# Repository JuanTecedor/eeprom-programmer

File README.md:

This is a fork of the Ben Eater's version of the EEPROM programmer, originally licensed under MIT LICENSE.

I did not like the fact of having it on a breadboard or buying it so I made a PCB.

~~I still have to solder and check that the circuit is working.~~
~~When I'm sure it's working I will upload the KiCad files.~~
It looks like it is working.

TODO:
  I will also do my own version of the code.
  Documentation

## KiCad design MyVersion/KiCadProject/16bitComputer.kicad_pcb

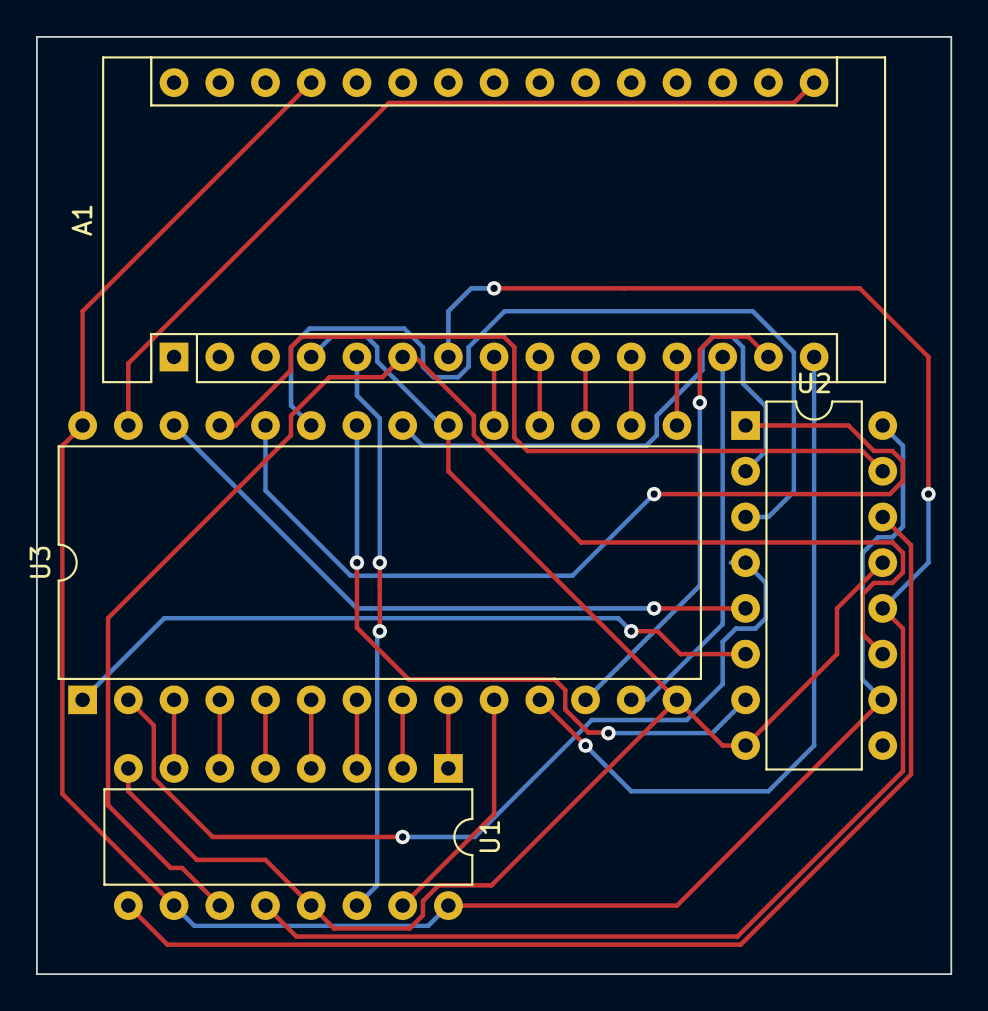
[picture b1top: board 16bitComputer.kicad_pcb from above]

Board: 2 copper layers, 50.8 x 52.1 mm, 4 parts (0 on the bottom side), 31 nets.

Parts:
A1: Arduino_Nano_v3.x; Arduino_Nano
U1, U2: 74HC595; DIP-16_W7.62mm
U3: 28C256; DIP-28_W15.24mm

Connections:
GND: A1.4, U1.8, U1.13, U2.8, U2.13, U3.14, U3.20
unnamed: A1.5, U1.14
unnamed: A1.6, U1.11, U2.11
unnamed: A1.7, U1.12, U2.12
unnamed: A1.8, U3.19
unnamed: A1.9, U3.18
unnamed: A1.10, U3.17
unnamed: A1.11, U3.16
unnamed: A1.12, U3.15
unnamed: A1.13, U3.13
unnamed: A1.14, U3.12
unnamed: A1.15, U3.11
unnamed: A1.16, U3.27
unnamed: A1.27, U1.10, U1.16, U2.10, U2.16, U3.28
unnamed: U1.1, U3.9
unnamed: U1.2, U3.8
unnamed: U1.3, U3.7
unnamed: U1.4, U3.6
unnamed: U1.5, U3.5
unnamed: U1.6, U3.4
unnamed: U1.7, U3.3
unnamed: U1.9, U2.14
unnamed: U1.15, U3.10
unnamed: U2.1, U3.24
unnamed: U2.2, U3.21
unnamed: U2.3, U3.23
unnamed: U2.4, U3.2
unnamed: U2.5, U3.26
unnamed: U2.6, U3.1
unnamed: U2.7, U3.22
unnamed: U2.15, U3.25

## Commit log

2020-11-23 Uploading my files
2020-11-23 fixing README
2020-11-23 fixed README
2020-11-23 uploaded final result
